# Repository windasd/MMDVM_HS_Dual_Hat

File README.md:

# MMDVM_HS_Dual_Hat
MMDVM_HS_Hat 的雙工版本
DB9MAT DF2ET DO7EN

這張電路板使用 Andy CA6JAU 的 [MMDVM_HS](https://github.com/juribeparada/MMDVM_HS)。板上有兩顆 ADF7021，可以雙工運作，DMR 的兩個時槽都能用。

> [!NOTE]
> 這是 [phl0/MMDVM_HS_Dual_Hat](https://github.com/phl0/MMDVM_HS_Dual_Hat) 的 fork。除了原專案的 rev1.0～1.3，這裡另外加了：移轉到 KiCad 10、[版本 2.0 mini](#版本-20-mini)，以及[版本 3.0 研究版](#版本-30-研究版尚未製作)（加上 Meshtastic、GPS、電池和 1G 乙太網路的 96Boards 擴充板）和它的主機軟體、螢幕設計。

（r3.0 研究版的 3D 渲染圖；這張板子還沒有實際製作。）

## 改版紀錄

### 版本 1.0

首次發行。

### 版本 1.1

LED D4 和 D5 對調，與掃描順序一致。新增焊錫跳線 JP1，只在 Raspberry Pi 上使用時可以把它短接，它會把 BOOT1 接到 GND。BOOT0 由 GPIO 控制。這種情況下 2x3 排針可以不焊，節省空間。U1 和 U2 各放了一顆電感，用來實驗擴展 VCO，分別是 L11 和 L12，屬於選配，UHF 使用時不必安裝。背面的測試點 TP1、TP2 可以在韌體以 #define TEST_DAC 編譯時，量測解調器輸出的 SNR。

**不建議用這個版本（重新）生產！**

### 版本 1.2

電路板佈局中一條不小心被刪掉的 3v3 連線已經補回。BOM、Mouser 購物車和鋼網都與 rev1.1 相同。

### 版本 1.3

STlink 排針改成與 [MMDVM_HS_Hat](https://github.com/mathisschmieder/MMDVM_HS_Hat) 板子相同的腳位。OLED 和 STlink 排針互換位置。JP1 稍微移動。C44、C45、C46 移到更靠近 STM32F1 CPU 的位置。背面絲印加了一個表格，標示裝的是哪一種 TCXO，這對韌體很重要。BOM 和 Mouser 購物車不變。鋼網稍有變動；如果 C44-C46 用手焊，仍然可以用舊的鋼網。

### 版本 2.0 mini

全面重新設計的 4 層板佈局，採 Raspberry Pi Zero 尺寸（65 x 30 mm），用板上的陶瓷晶片天線取代 SMA 接頭。專案檔在 `hardware/r2.0-mini`，BOM 在 `hardware/r2.0-mini/BOM.csv`。

**天線注意事項：** 佈局用的晶片天線封裝／3D 模型是 Yageo ANT1204LL08R0870A，這是 870 MHz 的料。BOM 現在列的是 433 MHz 版本 ANT1204LL20R0433A（本體同為 12 x 4 mm，焊墊圖相同）。板上晶片天線一定要在實際的板子上調整匹配網路；70 cm 頻段預計要重新調整。

### 版本 3.0 研究版（尚未製作）

`hardware/r3.0-study` 是一張較大的 96Boards 擴充板，主機是 Bubblegum-96：保留 rev1.3 的 MMDVM 雙工熱點，再加上 Meshtastic、GPS、電池供電和 1G 乙太網路。

| 區塊 | 內容 |
|---|---|
| 主機 | Bubblegum-96（96Boards CE）。本板經 LS、HS 兩個擴充座連接，並以 12 V 反向供電給主機 |
| MMDVM | rev1.3 的 STM32F103＋兩顆 ADF7021，430～440 MHz 雙工；TJC 5 吋螢幕接它的 Nextion 埠 |
| Meshtastic | RAK4630（nRF52840＋SX1262），台灣 920～925 MHz。電源獨立，主機關機時也能用電池單獨運作；前面板有 OLED 和 MESH 鍵 |
| GPS | u-blox MAX-M10S，由 Meshtastic 控制，NMEA 和 PPS 也分一路給主機（gpsd、chrony）；有實體開關 |
| 電源 | 4 顆 18650 並聯（1S4P）。USB-C 充電：CH224A 向變壓器要 9 V，BQ25895 充電，輸入電流依最壞的變壓器限制。12 V、5 V 升壓和 3.5 V 升降壓；電池保護、電量計、電池總開關、電源鍵控制 |
| 網路 | LAN7500（USB 轉 1G 乙太網路）＋RJ45 |
| 板子 | 4 層，90.6 x 167.1 mm，L 形，阻抗控制；另有 26 x 20 mm 的前面板 |

**狀態：從來沒有製作或測試過。**

- 線路圖和電路板：ERC 0、DRC 0（含警告和絲印）、未連線 0、線路圖與電路板一致。各顆 IC 都對照過規格書，也做過一次獨立的線路審查。
- 製造檔已備齊，可以下單試產（JLCPCB 格式）。下單參數、注意事項和尚未確認的項目都在 `hardware/r3.0-study/FAB_NOTES.md`；建議先貼 2～3 片。
- 2026-11-17 粗估：電路板做 5 片、貼 2 片，連同元件約 US$950～1,050。其中約一半是固定費用，主要是擴充料的換料費。
- 主機軟體和螢幕設計也都還沒有實際執行過。

| 路徑 | 內容 |
|---|---|
| `docs/meshtastic-gps-study.md` | 設計紀錄：需求、架構、選料理由、每一輪修改，以及尚未確認的項目（第 16 節是送廠準備） |
| `hardware/r3.0-study/` | KiCad 專案：主板 `mmdvm_mesh`、前面板 `front_panel/`；`BOM.csv`、`FAB_NOTES.md`；`gen/` 是產生線路圖、電路板和製造檔的腳本 |
| `case/meshtastic-concept/` | 3D 列印外殼概念（STEP／STL 和預覽圖） |
| `software/bubblegum96/` | 主機軟體：裝置樹疊加檔（overlay）、MMDVM-Host／MMDVM-Display、閘道器與 BrandMeister 設定、低電量關機、GPS 開關監看、風扇、網路、Meshtastic 設定，以及 Pi-Star 移植 |
| `display/tjc8048x550/` | TJC8048X550 5 吋螢幕的畫面設計、協定說明和建置步驟（`.HMI`／`.tft` 檔本身要用廠商的編輯器做） |

## 移轉到 KiCad 10（2026）

兩個版本都已移轉到 KiCad 10（需要 KiCad 10.0 或更新版本才能開啟）。

* 所有符號和封裝都連結到 KiCad 10 標準庫，或 `libraries/` 裡共用的專案庫（`mmdvm_hs_dual_hat.kicad_sym`、`mmdvm_hs_dual_hat.pretty`）。「rescue」庫和快取庫已經移除。
* 接腳幾何與 KiCad 10 標準符號不同的符號（STM32F103C8Tx、ADF7021、Raspberry Pi 排針、CONN_*、USB_OTG、LD1117S33TR、GS2、天線、NC/NO 跳線）原封不動移到專案符號庫，所以不必重畫任何連線。
* 焊墊幾何很接近、DRC 也沒有出現新違規的封裝，換成 KiCad 10 的標準封裝。新的焊墊較大、會違反既有間距的零件，保留專案庫裡的原始幾何：rev1.3 的 U1、U2、U3、R15、R16、C4、C17、C18、C33、C39，以及 rev2.0-mini 的 U1、U2（散熱過孔）。rev2.0-mini 的 R15、U4、P3、P4、J2、J4 保留 `pkl` 封裝。
* **rev1.3 線路圖修正：** 2020 年重畫的線路圖把 STM32 的 VSS/VSSA 腳（8、23、35、47）留著沒接、TCXO X1 的 VDD 和 GND 畫反，OSC_IN/OSC_OUT 也對調了。電路板本身一直是正確的。線路圖已經修回與電路板及 2018 年的原始網表一致；如果在舊線路圖上執行「Update PCB from Schematic」，會讓 TCXO 反向供電。
* 線路圖與電路板一致（網路名稱、封裝、欄位）。
* ERC：為 GND、+5V、+3V3（rev1.3）以及 GND、+5V、穩壓器輸入（rev2.0-mini）加上 PWR_FLAG；ADF7021 第 33 腳（SWD，同步字偵測）改為輸出。只有 rev2.0-mini 還留著四個孤立標籤警告（SWD_TP1/2、D+/D-：rev1.3 留下來的訊號名稱）。
* DRC rev2.0-mini：焊錫跳線 J2/J4 改成 net-tie 封裝（焊墊 1-2 依設計相連），並允許防焊橋；晶片天線的絲印不再壓到焊墊；移除一段懸空的走線殘段。rev1.3：移除兩段 10 µm 的走線碎片。
* 剩下、已檢視過的 DRC 項目：rev1.3 的零件邊界（courtyard）重疊（MCU 旁的 C44/C45、U4 的縫合過孔、J1 的固定孔）、兩處只有單一輻條的散熱連接，rev2.0-mini 的兩個絲印間距警告，以及兩張板子上小於 0.8 mm 的絲印文字。
* rev2.0-mini 需要 `libraries/pkl` 子模組：用 `git clone --recursive` 複製，或執行 `git submodule update --init`。

## BOM

版本庫根目錄的 `BOM.csv`／`BOM.xlsx` 對應 rev1.3，`hardware/r2.0-mini/BOM.csv`／`BOM.xlsx` 對應 rev2.0-mini。兩者都是從線路圖匯出的。

零件供貨狀況在 2026 年 11 月查過。相對於原始 BOM 的變更：

| 元件編號 | 原料號 | 新料號 | 原因 |
|---|---|---|---|
| 100n 電容 | Vishay VJ0402V104ZXJCW1BC (Y5V) | Murata GCM155R71C104KA55D (X7R) | 已淘汰 |
| C52（rev1.3） | Murata GRM155C80J106ME11J | Murata GRT155C80J106ME13D | 停產 |
| C52（rev2.0-mini） | 0603 封裝上放了 0402 的料 | Samsung CL10A106KP8NNNC (10 V) | 尺寸錯誤 |
| C33、C34 | AVX 04025A220GAT2A | Kyocera AVX KGM05ACG1H220GH | 料號更新，同一顆料 |
| C47、C48 | Murata GRM1555C1H470FA01D | Murata GJM1555C1H470FB01D | NRND |
| C51 | AVX TPSA106K010T0900 | Kyocera AVX TPSA106K010R0900 | 規格相同，有庫存 |
| R3、R4 | Susumu RR0510P-3831-D | Panasonic ERA-2AEB3831X | 沒有庫存，改用 0.1 %（原為 0.5 %） |
| P1、P2 | TE 5-1814832-1 | TE 5-1814832-2 | 已被取代；同一份圖面 1814832 rev C，只有包裝不同（捲帶） |
| L9、L10 | 值為「100MHz」／「10u」 | 值為「70R@100MHz」 | Würth 74279277 是磁珠，MPN 本來就是對的 |
| rev2.0-mini U3、U4、J1、A1、A2 | 沒有料號 | STM32F103C8T6、TLV70233DBVR、Harwin M20-7832046、ANT1204LL20R0433A | 缺漏 |

`SPN` 欄位空白，表示無法核對 Mouser 料號（Mouser 會擋自動查詢），請用 MPN 在 Mouser 搜尋。查詢當下庫存偏少的零件：TE 36501E20NJTDG（L3、L4；替代料 Murata LQW15AN20NG80D，要重新確認射頻匹配）、Murata GCM1555C1H471JA16J（C21、C22；替代料 GRT1555C1H471JA02D）、Panasonic ERA-2AEB271X（R9、R10）。12.288 MHz 的板子，X1 用 ECS-TXO-3225-122.8-TR。

## 製造檔

`kicad-cli` 把 Gerber X2/Excellon、鑽孔圖、貼片座標 CSV、BOM 和線路圖 PDF 匯出到 `hardware/<rev>/production/`（不進 git；板子規格見該目錄的 `FAB_NOTES.md`）。rev1.3 的 0402 焊墊改了，需要新的鋼網；rev2.0-mini 背面有一顆 SMD 零件（A1）。

r3.0 研究版在 `hardware/r3.0-study` 目錄執行 `bash gen/make_production.sh` 產生，另外會輸出 JLCPCB 格式的 BOM 和貼片座標檔，以及需要手焊的零件清單。

下面舊的 Mouser 購物車是 rev1.0/rev1.1 用的，裡面仍然是已淘汰的零件。

rev1.0 的 Mouser 購物車在[這裡](https://www.mouser.com/ProjectManager/ProjectDetail.aspx?AccessID=561bb01347)。

[這個](https://www.mouser.com/ProjectManager/ProjectDetail.aspx?AccessID=24ea9d644e)是 rev1.1 的 Mouser 購物車。L11 和 L12 是選配。

## 韌體安裝

這個裝置可以疊在 RPi 上經 GPIO 埠連接，也可以單獨使用、經 USB 連接。兩種方式在編譯和上傳韌體時的處理不同。USB 連接需要支援 bootloader 的韌體，GPIO 版本則不需要。

USB 連接一開始要先安裝 bootloader，這需要接 STlink。完成之後，MMDVM_HS 韌體就可以經 USB 升級。例如裝了設定錯誤的韌體時，可以改用 STlink 連接當作備援。

### 安裝支援 bootloader 的韌體（USB 連接）

要經 USB 埠使用這個裝置，必須安裝 bootloader，並編譯支援 bootloader 的韌體。全新的裝置還不能用 USB，所以要用 USB 轉序列轉接器或 STlink。用 STlink 的做法如下：

```
user@host:/opt/MMDVM_HS$ make stlink-bl 
././STM32F10X_Lib/utils/linux64/st-flash write ./STM32F10X_Lib/utils/bootloader/generic_boot20_pc13.bin 0x8000000
2018-03-02T10:01:04 INFO src/usb.c: -- exit_dfu_mode
2018-03-02T10:01:04 INFO src/common.c: Loading device parameters....
2018-03-02T10:01:04 INFO src/common.c: Device connected is: F1 Medium-density device, id 0x20036410
2018-03-02T10:01:04 INFO src/common.c: SRAM size: 0x5000 bytes (20 KiB), Flash: 0x10000 bytes (64 KiB) in pages of 1024 bytes
2018-03-02T10:01:04 INFO src/common.c: Attempting to write 7160 (0x1bf8) bytes to stm32 address: 134217728 (0x8000000)
Flash page at addr: 0x08001800 erased
2018-03-02T10:01:04 INFO src/common.c: Finished erasing 7 pages of 1024 (0x400) bytes
2018-03-02T10:01:04 INFO src/common.c: Starting Flash write for VL/F0/F3 core id
2018-03-02T10:01:04 INFO src/common.c: Successfully loaded flash loader in sram
  6/6 pages written
2018-03-02T10:01:05 INFO src/common.c: Starting verification of write complete
2018-03-02T10:01:05 INFO src/common.c: Flash written and verified! jolly good!
././STM32F10X_Lib/utils/linux64/st-flash write bin/mmdvm_f1bl.bin 0x8002000
2018-03-02T10:01:05 INFO src/common.c: Loading device parameters....
2018-03-02T10:01:05 INFO src/common.c: Device connected is: F1 Medium-density device, id 0x20036410
2018-03-02T10:01:05 INFO src/common.c: SRAM size: 0x5000 bytes (20 KiB), Flash: 0x10000 bytes (64 KiB) in pages of 1024 bytes
2018-03-02T10:01:05 INFO src/common.c: Attempting to write 55016 (0xd6e8) bytes to stm32 address: 134225920 (0x8002000)
Flash page at addr: 0x0800f400 erased
2018-03-02T10:01:07 INFO src/common.c: Finished erasing 54 pages of 1024 (0x400) bytes
2018-03-02T10:01:07 INFO src/common.c: Starting Flash write for VL/F0/F3 core id
2018-03-02T10:01:07 INFO src/common.c: Successfully loaded flash loader in sram
 53/53 pages written
2018-03-02T10:01:12 INFO src/common.c: Starting verification of write complete
2018-03-02T10:01:13 INFO src/common.c: Flash written and verified! jolly good!
```

現在裝置應該可以當作 /dev/ttyACMx 使用。

之後如果要經 USB 更新 MMDVM_HS 韌體本身，可以用 dfu 上傳的方式。Config.h 的設定如下：

    #define MMDVM_HS_DUAL_HAT_REV10
    #define ENABLE_ADF7021
    #define DUPLEX

    #define ADF7021_14_7456

或
    #define ADF7021_12_2880

適用於裝 12.288MHz TCXO 的板子。

    #define STM32_USB_HOST
    #define ENABLE_SCAN_MODE

選用：

    #define SEND_RSSI_DATA
    #define SERIAL_REPEATER

用「make bl」編譯韌體，然後：

```
user@host:/opt/MMDVM_HS$ sudo make dfu devser=/dev/ttyACM3
././STM32F10X_Lib/utils/linux64/upload-reset /dev/ttyACM3 750
././STM32F10X_Lib/utils/linux64/dfu-util -D bin/mmdvm_f1bl.bin -d 1eaf:0003 -a 2 -R -R
dfu-util 0.7

Copyright 2005-2008 Weston Schmidt, Harald Welte and OpenMoko Inc.
Copyright 2010-2012 Tormod Volden and Stefan Schmidt
This program is Free Software and has ABSOLUTELY NO WARRANTY
Please report bugs to dfu-util@lists.gnumonks.org

Filter on vendor = 0x1eaf product = 0x0003
Opening DFU capable USB device... ID 1eaf:0003
Run-time device DFU version 0110
Found DFU: [1eaf:0003] devnum=0, cfg=1, intf=0, alt=2, name="STM32duino bootloader v1.0  Upload to Flash 0x8002000"
Claiming USB DFU Interface...
Setting Alternate Setting #2 ...
Determining device status: state = dfuIDLE, status = 0
dfuIDLE, continuing
DFU mode device DFU version 0110
Device returned transfer size 1024
No valid DFU suffix signature
Warning: File has no DFU suffix
bytes_per_hash=1100
Copying data from PC to DFU device
Starting download: [##################################################] finished!
state(8) = dfuMANIFEST-WAIT-RESET, status(0) = No error condition is present
Done!
Resetting USB to switch back to runtime mode
```

### 手動編譯與上傳（GPIO 連接）

韌體安裝的詳細步驟請看[這份](https://github.com/juribeparada/MMDVM_HS#build-de-firmware-and-upload-to-zumspot-rpi)說明。流程和 ZumSpot Pi 的安裝類似。可以使用 MMDVM_HS 裡預先設定好的腳本。手動編輯 Config.h 的話，需要這些設定：

在 Config.h 打開下列設定：

    #define MMDVM_HS_DUAL_HAT_REV10
    #define ENABLE_ADF7021
    #define DUPLEX
    #define ADF7021_14_7456
    #define STM32_USART1_HOST
    #define ENABLE_SCAN_MODE

選用：

    #define SEND_RSSI_DATA
    #define SERIAL_REPEATER

裝 12.288MHz TCXO 的板子則用

    #define ADF7021_12_2880

取代 14_7456 選項。

編譯韌體：

    make

確認兩個 BOOT 跳線設定如下：

    BOOT0: completey removed
    BOOT1: set to BOOT 1 -

最後把韌體上傳到 MMDVM_HS_Dual_Hat：

    sudo make mmdvm_hs_dual_hat

### 在 Pi-Star 裡更新

[PiStar](http://www.pistar.uk/) 內含一個程式，可以把預先編譯好的韌體燒進 MMDVM_HS_Dual_Hat。要在 PiStar 裡更新韌體，執行下列指令：

    $ rpi-rw
    $ pistar-mmdvmhshatflash hs_dual_hat

如果板子裝的是 12.288MHz TCXO，要用下列指令燒錄對應的韌體：

    $ pistar-mmdvmhshatflash hs_dual_hat-12mhz

## 授權
本專案以 Creative Commons Attribution-NonCommercial-ShareAlike 3.0 (CC-BY-NC-SA 3.0, https://creativecommons.org/licenses/by-nc-sa/3.0/) 授權條款釋出。只要註明出處、不更改授權條款，你可以自由修改和分享。你可以替自己和朋友做任意數量的板子，甚至可以賣給他們回收成本，**但嚴格禁止把它做成商業產品！不得以營利為目的製作和販賣這些板子！**

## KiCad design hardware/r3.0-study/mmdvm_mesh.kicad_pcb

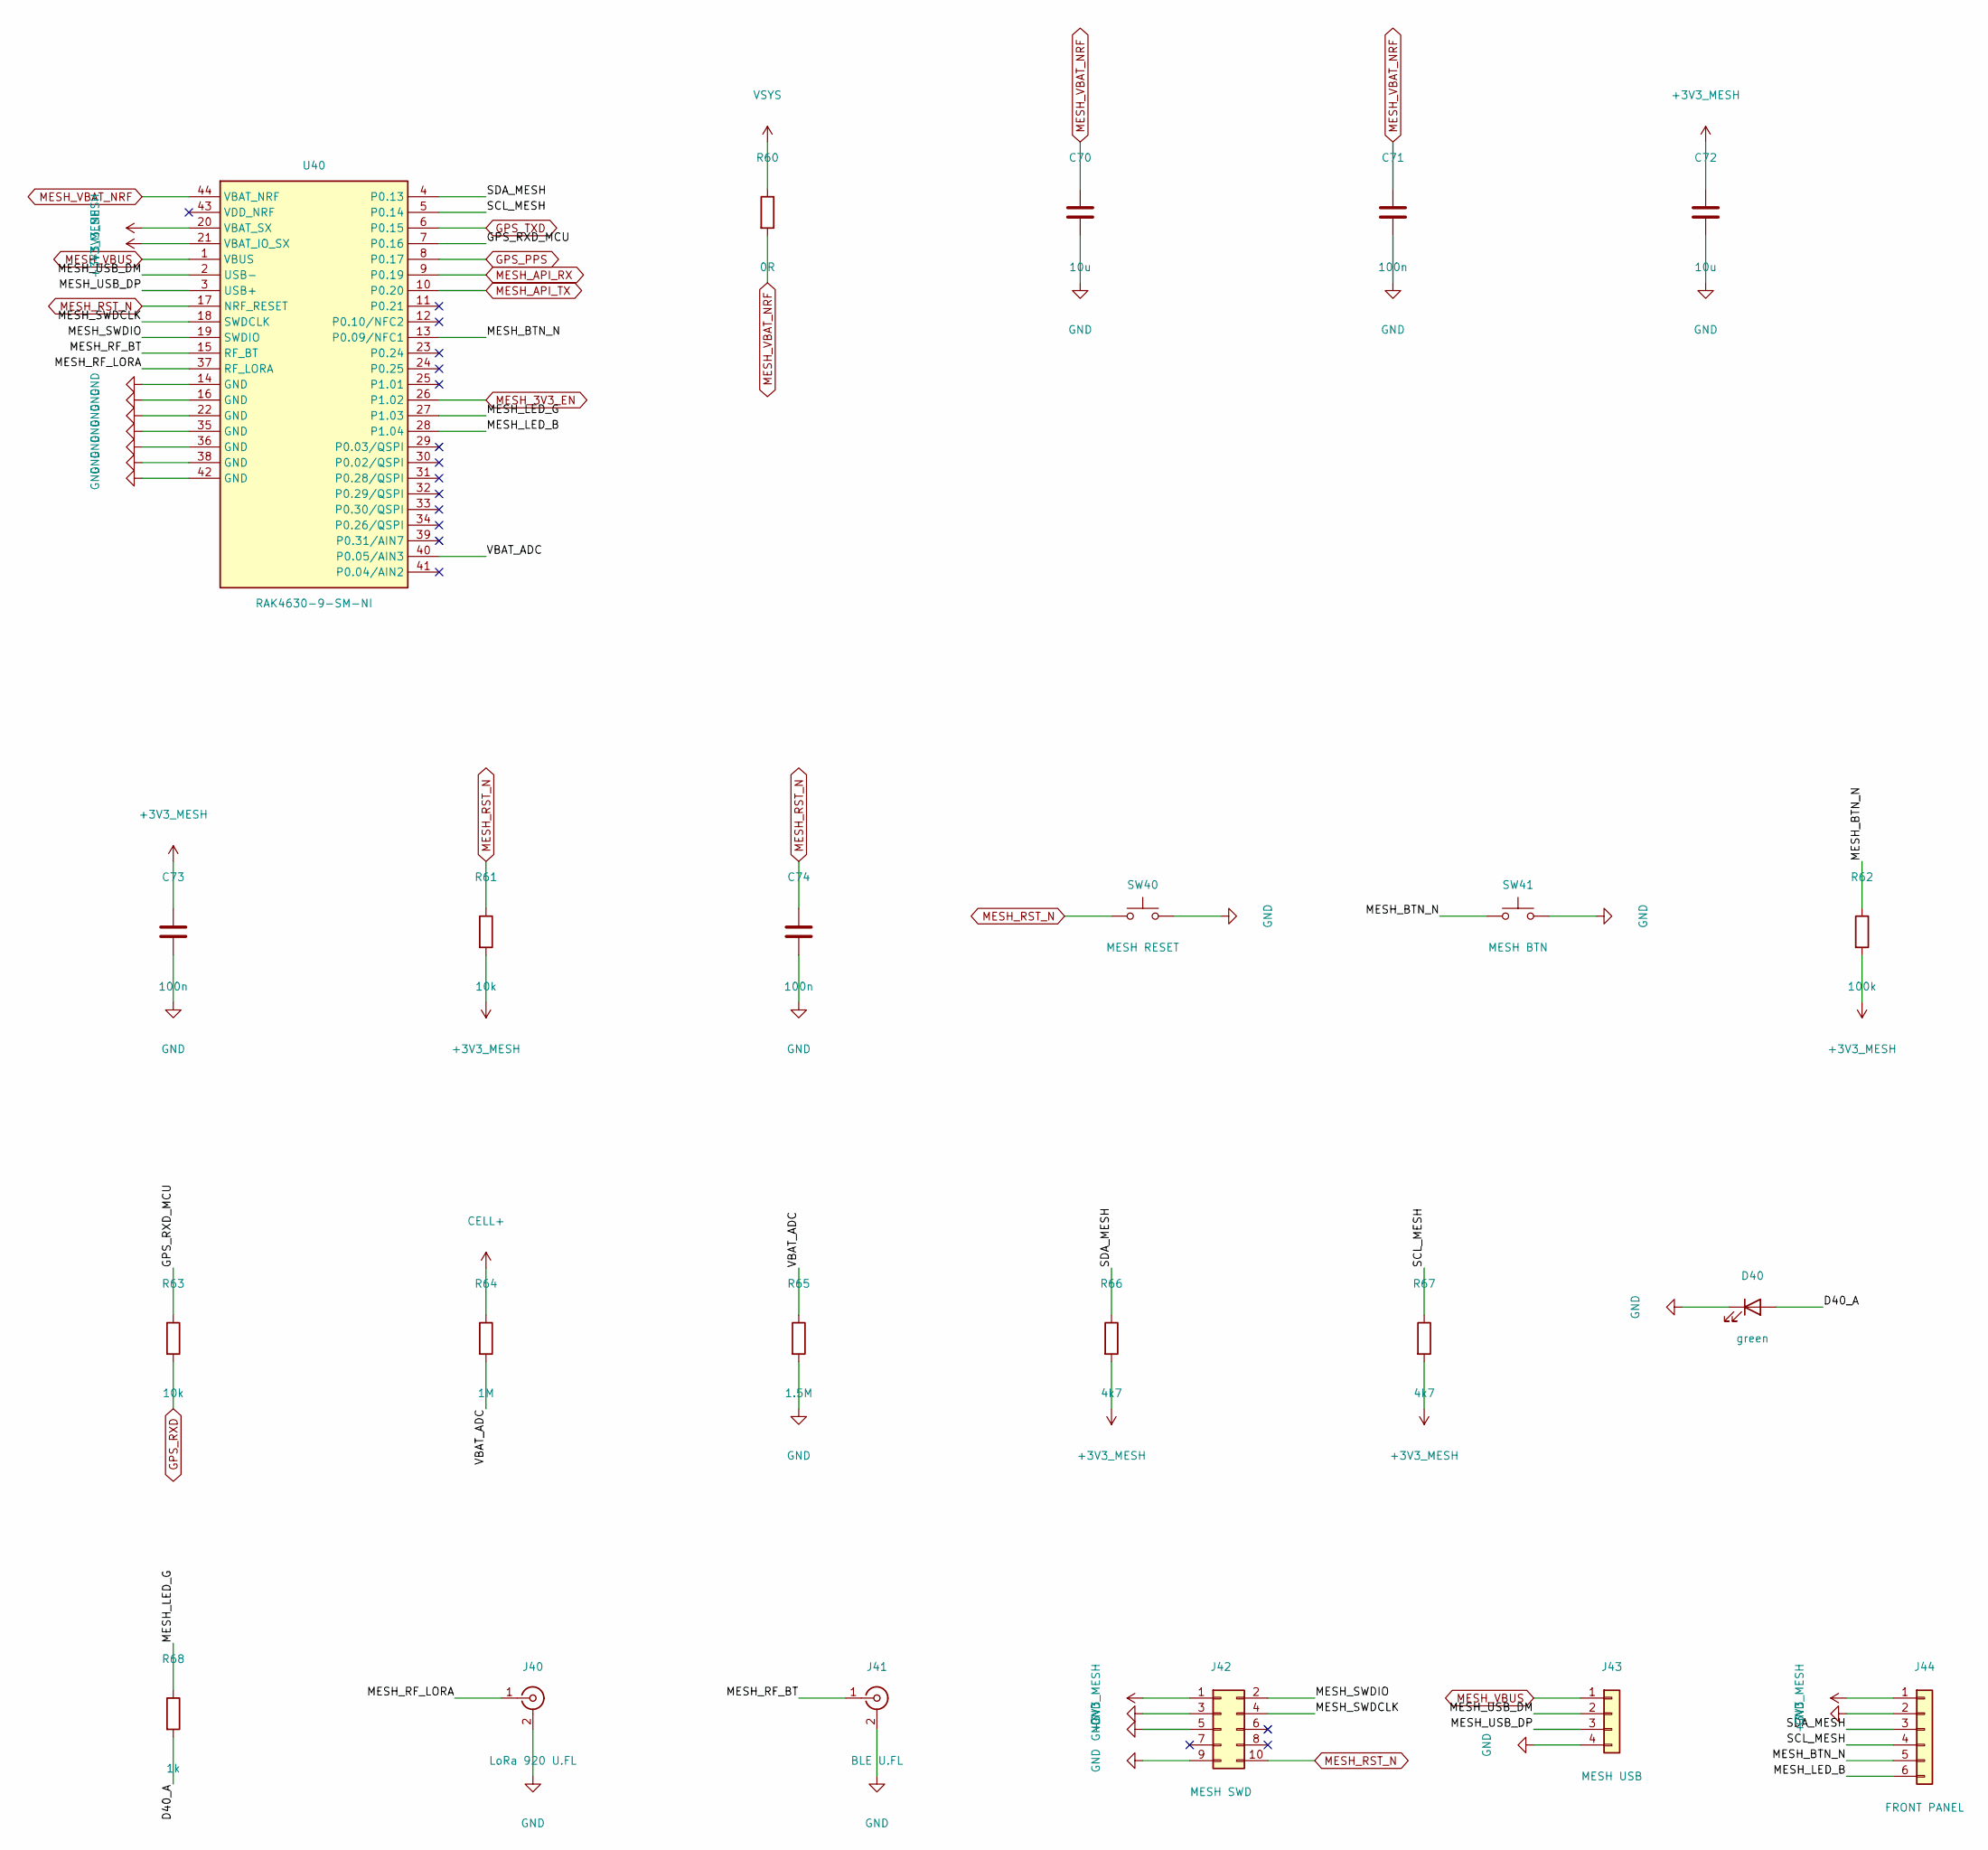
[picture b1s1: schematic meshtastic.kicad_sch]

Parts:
C70, C72: 10u; C_0603_1608Metric; MPN CL10A106MA8NRNC; Mouser 187-CL10A106MA8NRNC
C71, C73, C74: 100n; C_0402_1005Metric; MPN CL05B104KO5NNNC; Mouser 187-CL05B104KO5NNNC
D40: green; LED_0402_1005Metric; MPN APHHS1005LCGCK; Mouser 604-APHHS1005CGCK
J40: LoRa 920 U.FL; U.FL_Hirose_U.FL-R-SMT-1_Vertical; MPN U.FL-R-SMT-1(10); Mouser 798-U.FL-R-SMT-110
J41: BLE U.FL; U.FL_Hirose_U.FL-R-SMT-1_Vertical; MPN U.FL-R-SMT-1(10); Mouser 798-U.FL-R-SMT-110
J42: MESH SWD; PinHeader_2x05_P1.27mm_Vertical_SMD; MPN FTSH-105-01-F-DV-K; Mouser 200-FTSH10501FDVK
J43: MESH USB; JST_SH_SM04B-SRSS-TB_1x04-1MP_P1.00mm_Horizontal; MPN SM04B-SRSS-TB(LF)(SN); Mouser 306-SM04BSRSSTBLFSN
J44: FRONT PANEL; JST_SH_SM06B-SRSS-TB_1x06-1MP_P1.00mm_Horizontal; MPN SM06B-SRSS-TB(LF)(SN); Mouser 306-M06BSRSSTBLFSNPP
R60: 0R; R_0402_1005Metric; MPN 0402WGF0000TCE; Mouser 303-0402WGF0000TCE
R61, R63: 10k; R_0402_1005Metric; MPN 0402WGF1002TCE; Mouser 603-RC0402FR-0710KL
R62: 100k; R_0402_1005Metric; MPN 0402WGF1003TCE; Mouser 603-RC0402FR-07100KL
R64: 1M; R_0402_1005Metric; MPN 0402WGF1004TCE; Mouser 303-0402WGF1004TCE
R65: 1.5M; R_0402_1005Metric; MPN 0402WGF1504TCE; Mouser 708-RMCF0402FT1M50
R66, R67: 4k7; R_0402_1005Metric; MPN 0402WGF4701TCE; Mouser 603-RC0402FR-074K7L
R68: 1k; R_0402_1005Metric; MPN 0402WGF1001TCE; Mouser 603-RC0402FR-071KL
SW40: MESH RESET; SW_SPST_B3U-1000P; MPN B3U-1000P; Mouser 653-B3U-1000P
SW41: MESH BTN; SW_SPST_B3U-1000P; MPN B3U-1000P; Mouser 653-B3U-1000P
U40: RAK4630-9-SM-NI; RAK4630; MPN RAK4630-9-SM-NI; LCSC C42388202

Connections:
+3V3_MESH: C72.1, C73.1, J42.1, J44.1, R61.2, R62.2, R66.2, R67.2, U40.20 (VBAT_SX), U40.21 (VBAT_IO_SX); also elsewhere on the board
/Meshtastic/D40_A: D40.2 (A), R68.2
/Meshtastic/GPS_RXD_MCU: R63.1, U40.7 (P0.16)
/Meshtastic/MESH_BTN_N: J44.5, R62.1, SW41.1, U40.13 (P0.09/NFC1)
/Meshtastic/MESH_LED_B: J44.6, U40.28 (P1.04)
/Meshtastic/MESH_LED_G: R68.1, U40.27 (P1.03)
/Meshtastic/MESH_RF_BT: J41.1 (In), U40.15 (RF_BT)
/Meshtastic/MESH_RF_LORA: J40.1 (In), U40.37 (RF_LORA)
/Meshtastic/MESH_SWDCLK: J42.4, U40.18 (SWDCLK)
/Meshtastic/MESH_SWDIO: J42.2, U40.19 (SWDIO)
/Meshtastic/MESH_USB_DM: J43.2, U40.2 (USB-)
/Meshtastic/MESH_USB_DP: J43.3, U40.3 (USB+)
/Meshtastic/SCL_MESH: J44.4, R67.1, U40.5 (P0.14)
/Meshtastic/SDA_MESH: J44.3, R66.1, U40.4 (P0.13)
/Meshtastic/VBAT_ADC: R64.2, R65.1, U40.40 (P0.05/AIN3)
CELL+: R64.1; also elsewhere on the board
GND: C70.2, C71.2, C72.2, C73.2, C74.2, D40.1 (K), J40.2 (Ext), J41.2 (Ext), J42.3, J42.5, J42.9, J43.4, J44.2, R65.2, SW40.2, SW41.2, U40.14 (GND), U40.16 (GND), U40.22 (GND), U40.35 (GND), U40.36 (GND), U40.38 (GND), U40.42 (GND); also elsewhere on the board
GPS_PPS: U40.8 (P0.17); also elsewhere on the board
GPS_RXD: R63.2; also elsewhere on the board
GPS_TXD: U40.6 (P0.15); also elsewhere on the board
MESH_3V3_EN: U40.26 (P1.02); also elsewhere on the board
MESH_API_RX: U40.9 (P0.19); also elsewhere on the board
MESH_API_TX: U40.10 (P0.20); also elsewhere on the board
MESH_RST_N: C74.1, J42.10, R61.1, SW40.1, U40.17 (NRF_RESET); also elsewhere on the board
MESH_VBAT_NRF: C70.1, C71.1, R60.2, U40.44 (VBAT_NRF)
MESH_VBUS: J43.1, U40.1 (VBUS)
VSYS: R60.1; also elsewhere on the board

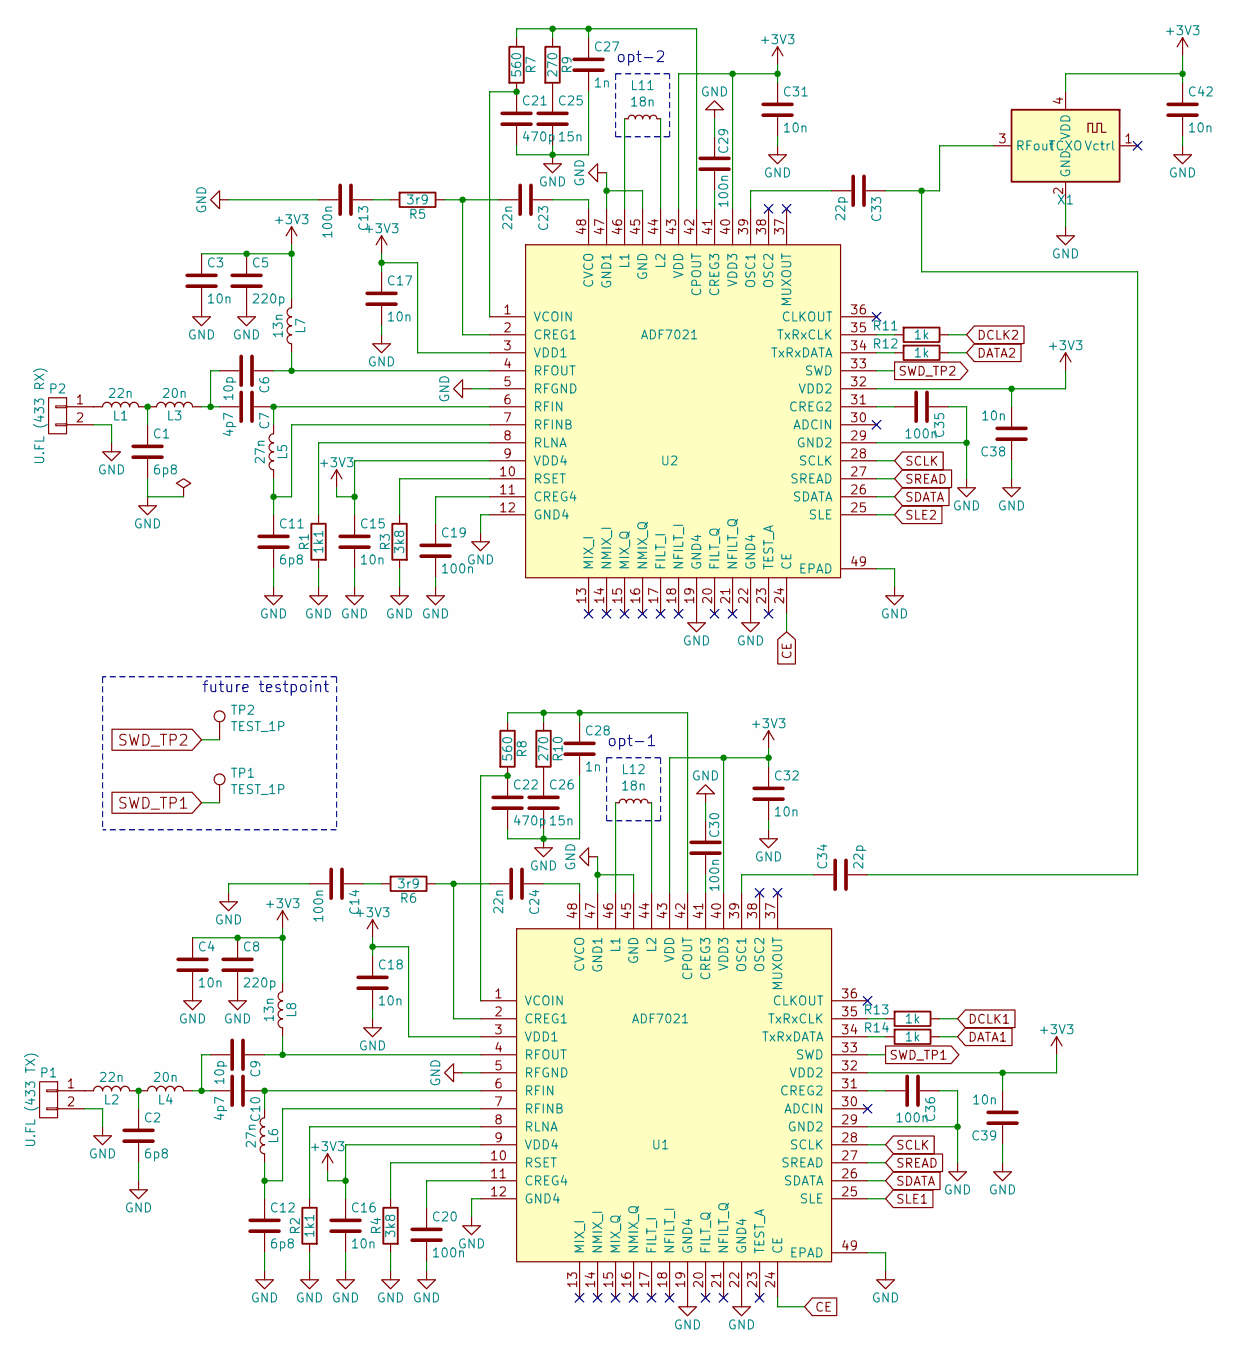
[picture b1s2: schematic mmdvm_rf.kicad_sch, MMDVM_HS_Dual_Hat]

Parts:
C1, C2, C11, C12: 6p8; C_0402_1005Metric; MPN GJM1555C1H6R8BB01D; Mouser 81-GJM1555C1H6R8BB1D
C3, C15, C16, C31, C32, C38, C42: 10n; C_0402_1005Metric; MPN VJ0402Y103KXJCW1BC; Mouser 77-VJ0402Y103KXJCBC
C4, C17, C18, C39: 10n; C_0402; MPN VJ0402Y103KXJCW1BC; Mouser 77-VJ0402Y103KXJCBC
C5, C8: 220p; C_0402_1005Metric; MPN GRM1555C1H221JA01D; Mouser 81-GRM1555C1H221JA01
C6, C9: 10p; C_0402_1005Metric; MPN GRM1555C1E100GA01D; Mouser 81-GRM1555C1E100GA1D
C7, C10: 4p7; C_0402_1005Metric; MPN GRM1555C1H4R7CA01D; Mouser 81-GRM1555C1H4R7CA1D
C13, C14, C19, C20, C29, C30, C35, C36: 100n; C_0402_1005Metric; MPN GCM155R71C104KA55D; Mouser 81-GCM155R71C104KA5J
C21, C22: 470p; C_0402_1005Metric; MPN GCM1555C1H471JA16J; Mouser 81-GCM1555C1H471JA6J
C23, C24: 22n; C_0402_1005Metric; MPN GCM155R71E223KA55D; Mouser 81-GCM155R71E223KA5D
C25, C26: 15n; C_0402_1005Metric; MPN GRM155R71C153KA01J; Mouser 81-GRM155R71C153KA1J
C27, C28: 1n; C_0402_1005Metric; MPN GRM155R60J102KA01D; Mouser 81-GRM155R60J102KA1D
C33: 22p; C_0402; MPN KGM05ACG1H220GH; Mouser 581-KGM05ACG1H220GH
C34: 22p; C_0402_1005Metric; MPN KGM05ACG1H220GH; Mouser 581-KGM05ACG1H220GH
L1, L2: 22n; L_0402_1005Metric; MPN LQW15CA22NJ00D; Mouser 81-LQW15CA22NJ00D
L3, L4: 20n; L_0402_1005Metric; MPN 36501E20NJTDG; Mouser 279-36501E20NJTDG
L5, L6: 27n; L_0402_1005Metric; MPN LQW15AN27NG80D; Mouser 81-LQW15AN27NG80D
L7, L8: 13n; L_0402_1005Metric; MPN LQW15AN13NG80D; Mouser 81-LQW15AN13NG80D
L11, L12: 18n; L_0402_1005Metric; MPN 36501E18NJTDG; Mouser 279-36501E18NJTDG
P1: U.FL (433 TX); U.FL_Hirose_U.FL-R-SMT-1_Vertical; MPN U.FL-R-SMT-1(10); Mouser 798-U.FL-R-SMT-110
P2: U.FL (433 RX); U.FL_Hirose_U.FL-R-SMT-1_Vertical; MPN U.FL-R-SMT-1(10); Mouser 798-U.FL-R-SMT-110
R1, R2: 1k1; R_0402_1005Metric; MPN RR0510P-112-D; Mouser 754-RR0510P-112D
R3, R4: 3k8; R_0402_1005Metric; MPN ERA-2AEB3831X; Mouser 667-ERA-2AEB3831X
R5, R6: 3r9; R_0402_1005Metric; MPN CRCW04023R90JNED; Mouser 71-CRCW0402J-3.9-E3
R7, R8: 560; R_0402_1005Metric; MPN ERA-2AEB561X; Mouser 667-ERA-2AEB561X
R9, R10: 270; R_0402_1005Metric; MPN ERA-2AEB271X; Mouser 667-ERA-2AEB271X
R11, R12, R13, R14: 1k; R_0402_1005Metric; MPN RCS04021K00JNED; Mouser 71-RCS04021K00JNED
TP1, TP2: TEST_1P; TestPoint_Pad_1.0x1.0mm
U1, U2: ADF7021; QFN-48-1EP_7x7mm_Pitch0.5mm; MPN ADF7021BCPZ; Mouser 584-ADF7021BCPZ
X1: TCXO; Crystal_SMD_3225-4Pin_3.2x2.5mm; MPN ECS-TXO-3225-147.4-TR; Mouser 520-TXO-3225-14.74T

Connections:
+3V3: C3.1, C4.1, C5.1, C8.1, C15.1, C16.1, C17.1, C18.1, C31.1, C32.1, C38.2, C39.2, C42.1, L7.2, L8.2, U1.3 (VDD1), U1.9 (VDD4), U1.32 (VDD2), U1.40 (VDD3), U1.43 (VDD), U2.3 (VDD1), U2.9 (VDD4), U2.32 (VDD2), U2.40 (VDD3), U2.43 (VDD), X1.4 (VDD); also elsewhere on the board
CE: U1.24 (CE), U2.24 (CE); also elsewhere on the board
DATA1: R14.1; also elsewhere on the board
DATA2: R12.1; also elsewhere on the board
DCLK1: R13.1; also elsewhere on the board
DCLK2: R11.1; also elsewhere on the board
GND: C1.2, C2.2, C3.2, C4.2, C5.2, C8.2, C11.2, C12.2, C13.2, C14.2, C15.2, C16.2, C17.2, C18.2, C19.2, C20.2, C21.2, C22.2, C25.2, C26.2, C27.2, C28.2, C29.1, C30.1, C31.2, C32.2, C35.1, C36.1, C38.1, C39.1, C42.2, P1.2, P2.2, R1.2, R2.2, R3.2, R4.2, U1.5 (RFGND), U1.12 (GND4), U1.19 (GND4), U1.22 (GND4), U1.29 (GND2), U1.45 (GND), U1.47 (GND1), U1.49 (EPAD), U2.5 (RFGND), U2.12 (GND4), U2.19 (GND4), U2.22 (GND4), U2.29 (GND2), U2.45 (GND), U2.47 (GND1), U2.49 (EPAD), X1.2 (GND); also elsewhere on the board
unnamed: C1.1, L1.2, L3.1
unnamed: C2.1, L2.2, L4.1
unnamed: C6.2, C7.2, L3.2
unnamed: C9.2, C10.2, L4.2
unnamed: C13.1, R5.2
unnamed: C14.1, R6.2
unnamed: C25.1, R9.2
unnamed: C26.1, R10.2
unnamed: L2.1, P1.1
unnamed: L1.1, P2.1
unnamed: C28.1, R8.1, R10.1, U1.42 (CPOUT)
unnamed: C24.2, R6.1, U1.2 (CREG1)
unnamed: C36.2, U1.31 (CREG2)
unnamed: C30.2, U1.41 (CREG3)
unnamed: C20.1, U1.11 (CREG4)
unnamed: C24.1, U1.48 (CVCO)
unnamed: L12.1, U1.46 (L1)
unnamed: L12.2, U1.44 (L2)
unnamed: C34.1, U1.39 (OSC1)
unnamed: C10.1, L6.2, U1.6 (RFIN)
unnamed: C12.1, L6.1, U1.7 (RFINB)
unnamed: C9.1, L8.1, U1.4 (RFOUT)
unnamed: R2.1, U1.8 (RLNA)
unnamed: R4.1, U1.10 (RSET)
unnamed: R13.2, U1.35 (TxRxCLK)
unnamed: R14.2, U1.34 (TxRxDATA)
unnamed: C22.1, R8.2, U1.1 (VCOIN)
unnamed: C27.1, R7.1, R9.1, U2.42 (CPOUT)
unnamed: C23.2, R5.1, U2.2 (CREG1)
unnamed: C35.2, U2.31 (CREG2)
unnamed: C29.2, U2.41 (CREG3)
unnamed: C19.1, U2.11 (CREG4)
unnamed: C23.1, U2.48 (CVCO)
unnamed: L11.1, U2.46 (L1)
unnamed: L11.2, U2.44 (L2)
unnamed: C33.2, U2.39 (OSC1)
unnamed: C7.1, L5.2, U2.6 (RFIN)
unnamed: C11.1, L5.1, U2.7 (RFINB)
unnamed: C6.1, L7.1, U2.4 (RFOUT)
unnamed: R1.1, U2.8 (RLNA)
unnamed: R3.1, U2.10 (RSET)
unnamed: R11.2, U2.35 (TxRxCLK)
unnamed: R12.2, U2.34 (TxRxDATA)
unnamed: C21.1, R7.2, U2.1 (VCOIN)
unnamed: C33.1, C34.2, X1.3 (RFout)
SCLK: U1.28 (SCLK), U2.28 (SCLK); also elsewhere on the board
SDATA: U1.26 (SDATA), U2.26 (SDATA); also elsewhere on the board
SLE1: U1.25 (SLE); also elsewhere on the board
SLE2: U2.25 (SLE); also elsewhere on the board
SREAD: U1.27 (SREAD), U2.27 (SREAD); also elsewhere on the board
SWD_TP1: TP1.1, U1.33 (SWD)
SWD_TP2: TP2.1, U2.33 (SWD)

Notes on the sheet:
opt-1
future testpoint
opt-2
